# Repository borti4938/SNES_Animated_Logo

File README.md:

### Animated Logo for the SNES
---

This is an earlier project. This project is not under development anymore. Documentation is rather simple or simply not present.

Please don't write me for any support. Please reach out to community forums and use the knowledge and experiences there.

Best Regards, Peter

---

### From Original README

##### Installation

The PCB is designed to be assembled to the extension port of the ‘normal’ SNES.
/Rst is a combination of a pad and a jumper, which can be used as follows:
– connect the pad with a wire to CIC pad 10 (animation is repeated on a reset using reset button and the IGR (PIC-microcontroller code)
– close jumper: animation is repeated on every reset (I do not like this, e.g., because the sd2snes performs a reset on startup and the animation is started a second time while the initial animation is running)
– neither connect the wire or the close the jumper: animation is just played once

##### Others:

- Software: http://circuit-board.de/forum/index.php/Thread/7573-Super-Nintendo-Beleuchtetes-animiertes-Logo/ (can now be accessed here, too)
- Fuse Bits for the ATTiny45: lfuse: 0xe2, hfuse:w:0xdf
- The given resistor values for the LEDs (2x 180Ohm (yellow, red) and 2x 120Ohm (green, blue)) are just examples. You may adjust these values according to your needs :)
- LEDs are in 0805 or P-LCC-2 package.

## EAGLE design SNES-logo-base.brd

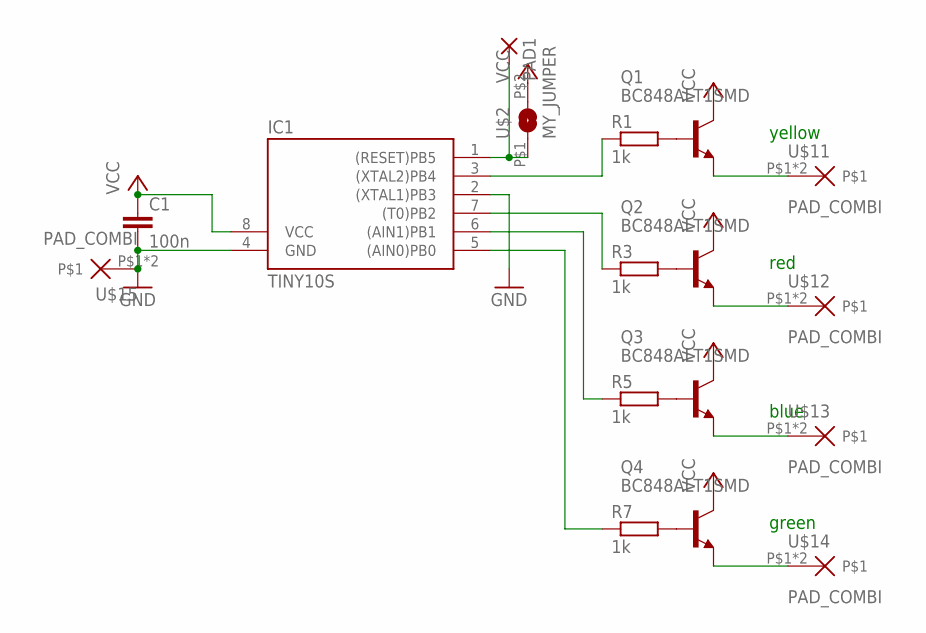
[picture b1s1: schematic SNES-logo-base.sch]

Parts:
C1: 100n; Z0805
IC1: TINY10S; SOIC8
PAD1: SMD2; SMD1,27-2,54
Q1, Q2, Q3, Q4: BC848ALT1SMD; SOT23
R1, R3, R5, R7: 1k; Z0805
U$2: MY_JUMPER; MYJUMP
U$11, U$12, U$13, U$14, U$15: PAD_COMBI

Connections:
GND: C1.2, IC1.2 ((XTAL1)PB3), IC1.4 (GND), U$15.P$1, U$15.P$2
unnamed: Q2.2 (E), U$12.P$1, U$12.P$2
unnamed: IC1.1 ((RESET)PB5), PAD1.1, U$2.P$1 (1)
unnamed: Q3.2 (E), U$13.P$1, U$13.P$2
unnamed: Q1.1 (B), R1.2
unnamed: Q2.1 (B), R3.2
unnamed: Q3.1 (B), R5.2
unnamed: Q4.1 (B), R7.2
unnamed: Q4.2 (E), U$14.P$1, U$14.P$2
unnamed: Q1.2 (E), U$11.P$1, U$11.P$2
unnamed: IC1.3 ((XTAL2)PB4), R1.1
unnamed: IC1.7 ((T0)PB2), R3.1
unnamed: IC1.6 ((AIN1)PB1), R5.1
unnamed: IC1.5 ((AIN0)PB0), R7.1
VCC: C1.1, IC1.8 (VCC), Q1.3 (C), Q2.3 (C), Q3.3 (C), Q4.3 (C), U$2.P$2 (2)

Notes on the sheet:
yellow
red
blue
green

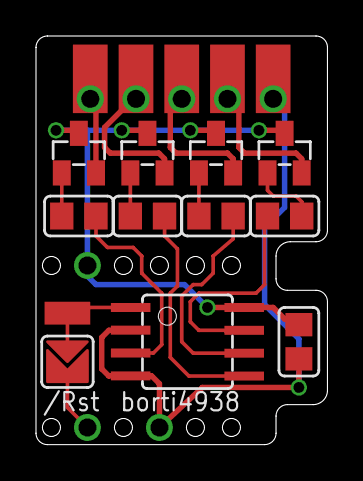
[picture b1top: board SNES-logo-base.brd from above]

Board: 2 copper layers, 16.2 x 22.7 mm, 17 parts (0 on the bottom side), 15 nets.

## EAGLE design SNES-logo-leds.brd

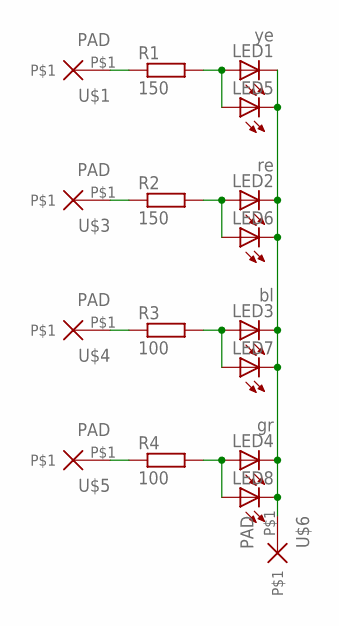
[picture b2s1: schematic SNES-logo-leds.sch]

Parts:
LED1: ye; SML0805
LED2: re; SML0805
LED3: bl; SML0805
LED4: gr; SML0805
LED5, LED6, LED7, LED8: LEDP-LCC-2; P-LCC-2
R1, R2: 150; Z0805
R3, R4: 100; Z0805
U$1, U$3, U$4, U$5, U$6: PAD

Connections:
unnamed: LED1.C, LED2.C, LED3.C, LED4.C, LED5.C, LED6.C, LED7.C, LED8.C, U$6.P$1
unnamed: R2.1, U$3.P$1
unnamed: LED1.A, LED5.A, R1.2
unnamed: R1.1, U$1.P$1
unnamed: R3.1, U$4.P$1
unnamed: R4.1, U$5.P$1
unnamed: LED2.A, LED6.A, R2.2
unnamed: LED3.A, LED7.A, R3.2
unnamed: LED4.A, LED8.A, R4.2

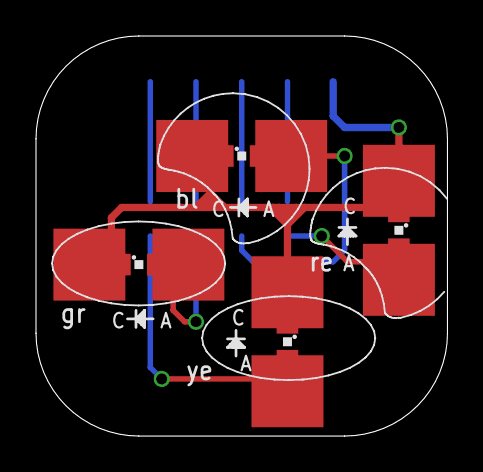
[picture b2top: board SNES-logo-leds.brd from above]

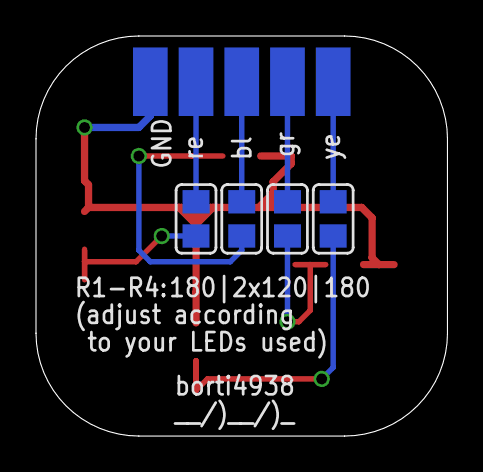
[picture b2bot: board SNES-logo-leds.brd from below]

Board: 2 copper layers, 22.9 x 22.2 mm, 17 parts (9 on the bottom side), 9 nets.

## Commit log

2020-05-03 initial commit for archive
